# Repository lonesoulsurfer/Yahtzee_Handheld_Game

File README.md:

# Yahtzee - Handheld Game with an Optimal AI Brain

YouTube - https://youtu.be/DMBQGAXjRF4

Instructables - https://www.instructables.com/Yahtzee-Raspberry-Pi-Handheld-Game/

---

## Two Versions of the Firmware

There are two versions of the game engine's "brain", and both are available to download and try from this repo:

- **V1, the Machine Learning brain.** The original approach: hand-built heuristics, probability tables, and a set of weighted priorities that adjust over time through self-play, stored in EEPROM. See the [V1 Overview](#v1-overview-the-machine-learning-brain) below.
- **V2, the Optimal "V-Brain".** The current version, and the one the rest of this README focuses on. It replaces the learned weights with an exact, mathematically solved decision table. See [How V2 Works](#how-v2-works-the-optimal-v-brain) below.

Both firmware versions are fully playable and included in this repo (`Yahtzee_v1.ino` / `Yahtzee_v2.ino`) if you want to compare them, or if you just prefer the adaptive feel of V1.

---

## V1 Overview: The Machine Learning Brain

V1 started out rule based, then grew into a probability and weights system. It uses hardcoded probability tables (for straights and of-a-kinds) to work out expected value, then adjusts its priorities, things like Yahtzee chasing, upper bonus feasibility, and endgame aggression, using a set of learned weights. Those weights live in EEPROM and shift over time based on self-play (the "Train AI" tool runs four personality variants against each other) and on how the human opponent plays.

It's a genuinely adaptive system. It gets tougher the more you play it, and it reads your playing style to adjust its own. But it's still fundamentally an approximation: the weights are a best guess at what matters in a given situation, tuned by trial and error rather than worked out from the actual maths of the game, and it needs a run-up of games before its learned behaviour is any good.

---

## How V2 Works: The Optimal V-Brain

V2 throws out the heuristics and weights entirely and replaces them with an exact solution, worked out once using dynamic programming and baked into a lookup table (`vtable.h`) that ships with the firmware. Rather than estimating the best move, V2 looks up the true expected value of every possible decision for the exact game state it's in, and simply picks the best one.

### The Value Table

`vtable.h` contains a solved value for every combination of:
- Which of the 13 scoring categories are still open (the "scorecard mask")
- The current upper section running total (capped at 63, since anything beyond that doesn't matter to the bonus)
- Whether a Yahtzee has already been scored (which changes what future Yahtzees are worth, thanks to the 100 point bonus)

For any of those states, the table gives the true expected final score from that point onward, assuming optimal play. This was worked out offline by starting from the end of the game and working backwards (a classic dynamic programming approach), so every value in the table is provably correct, not estimated.

### Making a Decision

On every roll, the V-brain does the following:
1. Sorts the current dice and looks up which of the 252 possible dice states it's in.
2. For each way it could hold some subset of the dice, works out the expected value of rerolling the rest, by weighting every possible reroll outcome by its true probability and looking up the resulting value in the table.
3. Compares that against simply stopping and scoring the best available category right now.
4. Picks whichever option has the higher expected value. No weights, no priority list, just the actual numbers.

This same lookup approach handles category selection too. Once the game engine stops rolling, it checks the value of scoring in every open category and takes the one with the highest true expected value, correctly accounting for the upper section bonus and the cost of spending a good category on a mediocre roll.

### Why It's Better

V1's weights can only ever approximate optimal play, and they need games (and EEPROM wear) to converge toward something good. V2's table already is the optimal policy. There's nothing to learn or converge toward, so it plays at maximum strength from the very first roll of the very first game, every single game. The trade-off is that V2 no longer profiles or adapts to a specific human opponent the way V1's learning system did. It isn't trying to be adaptive, it's trying to be correct.

### Still Carried Over from V1

A few things didn't need reinventing, so V2 keeps them as is:
- **Timeout protection.** If the game engine takes more than 30 seconds to decide, a watchdog forces it to pick the best available category and resets its state, so the game can never hang.
- **Stats tracking.** Win/loss history, high scores, and Yahtzee counts are still tracked and stored in EEPROM for the stats screens, even though none of it feeds back into how the V-brain plays.

---

## A Note on God Mode / Difficulty

V1's Normal / Hard / God Mode difficulty levels changed how aggressively the game engine would reroll. In V2, difficulty no longer changes how the AI plays. The V-brain always plays the mathematically optimal move, since there's no such thing as a "more optimal than optimal" setting. It is still beatable, since Yahtzee has a meaningful luck component, but you're playing against the best possible strategy on every roll.

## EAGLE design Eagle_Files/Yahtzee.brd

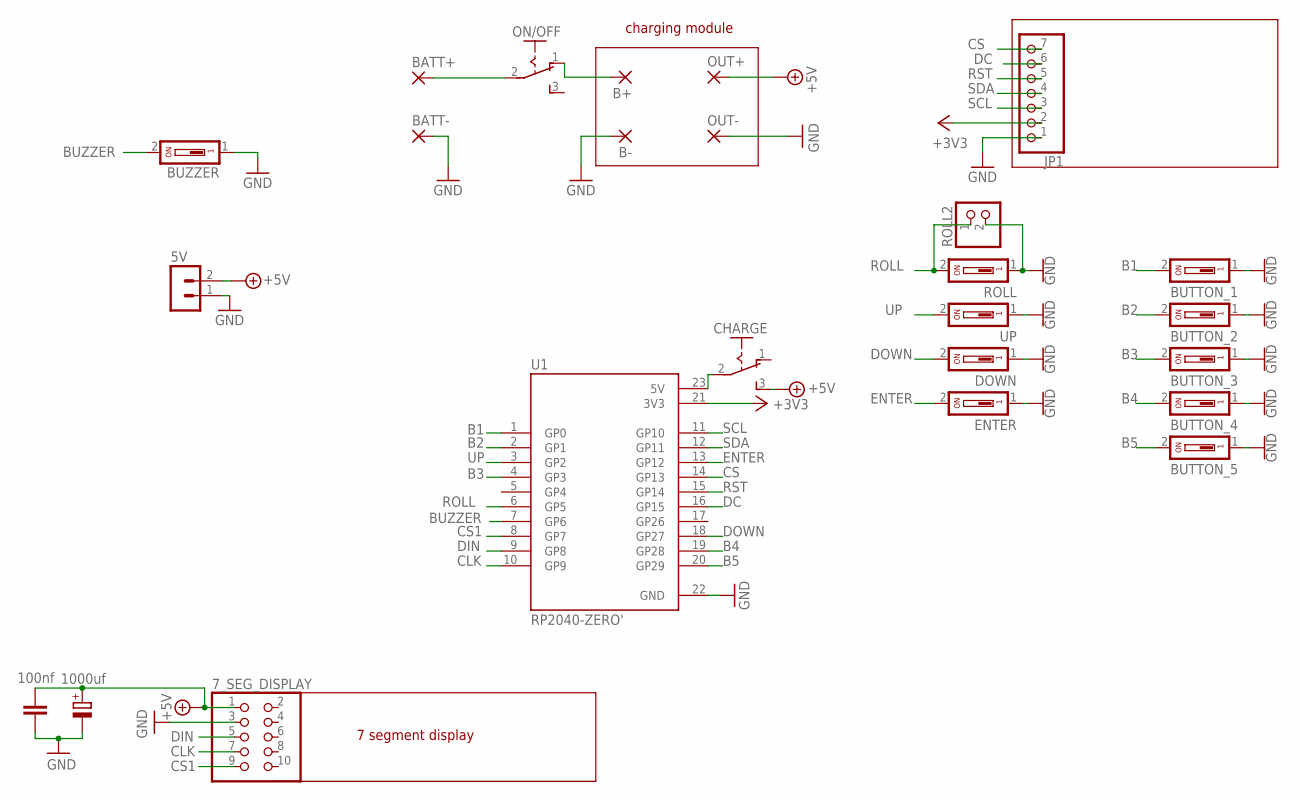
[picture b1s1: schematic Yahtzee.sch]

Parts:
5V: B2B-PH-K-S
7_SEG_DISPLAY: PINHD-2X5; 2X05
B+: SMD5; SMD2,54-5,08
B-: SMD5; SMD2,54-5,08
BATT+: SMD5; SMD2,54-5,08
BATT-: SMD5; SMD2,54-5,08
BUTTON_1, BUTTON_2, BUTTON_3, BUTTON_4, BUTTON_5: DS01; DS-01
BUZZER: DS01; DS-01
C1: 100nf; C050-024X044
C2: 1000uf; E2,5-7
CHARGE: M251
DOWN: DS01; DS-01
ENTER: DS01; DS-01
JP1: PINHD-1X7; 1X07
ON/OFF: M251
OUT+: SMD5; SMD2,54-5,08
OUT-: SMD5; SMD2,54-5,08
ROLL: DS01; DS-01
ROLL2: PINHD-1X2; 1X02
U1: RP2040-ZERO'; MODULE_RP2040-ZERO
UP: DS01; DS-01

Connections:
+3V3: JP1.2, U1.21 (3V3)
+5V: 5V.2, 7_SEG_DISPLAY.1, C1.1, C2.+, CHARGE.3 (S), OUT+.1
B1: BUTTON_1.2, U1.1 (GP0)
B2: BUTTON_2.2, U1.2 (GP1)
B3: BUTTON_3.2, U1.4 (GP3)
B4: BUTTON_4.2, U1.19 (GP28)
B5: BUTTON_5.2, U1.20 (GP29)
BUZZER: BUZZER.2, U1.7 (GP6)
CLK: 7_SEG_DISPLAY.7, U1.10 (GP9)
CS: JP1.7, U1.14 (GP13)
CS1: 7_SEG_DISPLAY.9, U1.8 (GP7)
DC: JP1.6, U1.16 (GP15)
DIN: 7_SEG_DISPLAY.5, U1.9 (GP8)
DOWN: DOWN.2, U1.18 (GP27)
ENTER: ENTER.2, U1.13 (GP12)
GND: 5V.1, 7_SEG_DISPLAY.3, B-.1, BATT-.1, BUTTON_1.1, BUTTON_2.1, BUTTON_3.1, BUTTON_4.1, BUTTON_5.1, BUZZER.1, C1.2, C2.-, DOWN.1, ENTER.1, JP1.1, OUT-.1, ROLL.1, ROLL2.2, U1.22 (GND), UP.1
unnamed: BATT+.1, ON/OFF.2
unnamed: B+.1, ON/OFF.1 (O)
unnamed: CHARGE.2, U1.23 (5V)
ROLL: ROLL.2, ROLL2.1, U1.6 (GP5)
RST: JP1.5, U1.15 (GP14)
SCL: JP1.3, U1.11 (GP10)
SDA: JP1.4, U1.12 (GP11)
UP: U1.3 (GP2), UP.2

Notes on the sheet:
charging module
7 segment display

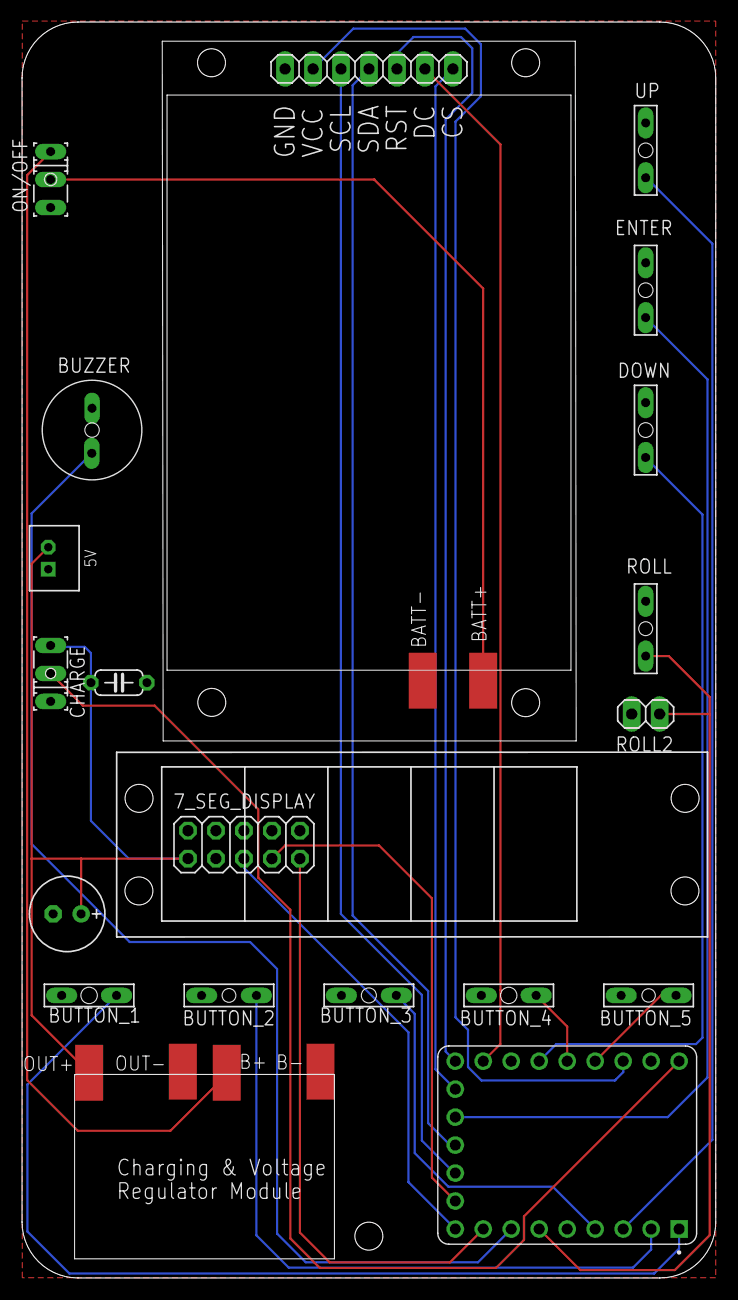
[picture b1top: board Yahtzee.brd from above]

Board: 2 copper layers, 63.0 x 114.0 mm, 25 parts (0 on the bottom side), 24 nets.

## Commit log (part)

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2026-04-23 Remove all content from README.md
2026-04-23 Add files via upload
    download both files and load up the Yahtzee_v1 one. the blackjack INO file will also be included when you load the Yahtzee one.

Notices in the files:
parts and their libraries:
SparkFun-PowerSymbols: Licensing: Creative Commons ShareAlike 4.0 International - https://creativecommons.org/licenses/by-sa/4.0
